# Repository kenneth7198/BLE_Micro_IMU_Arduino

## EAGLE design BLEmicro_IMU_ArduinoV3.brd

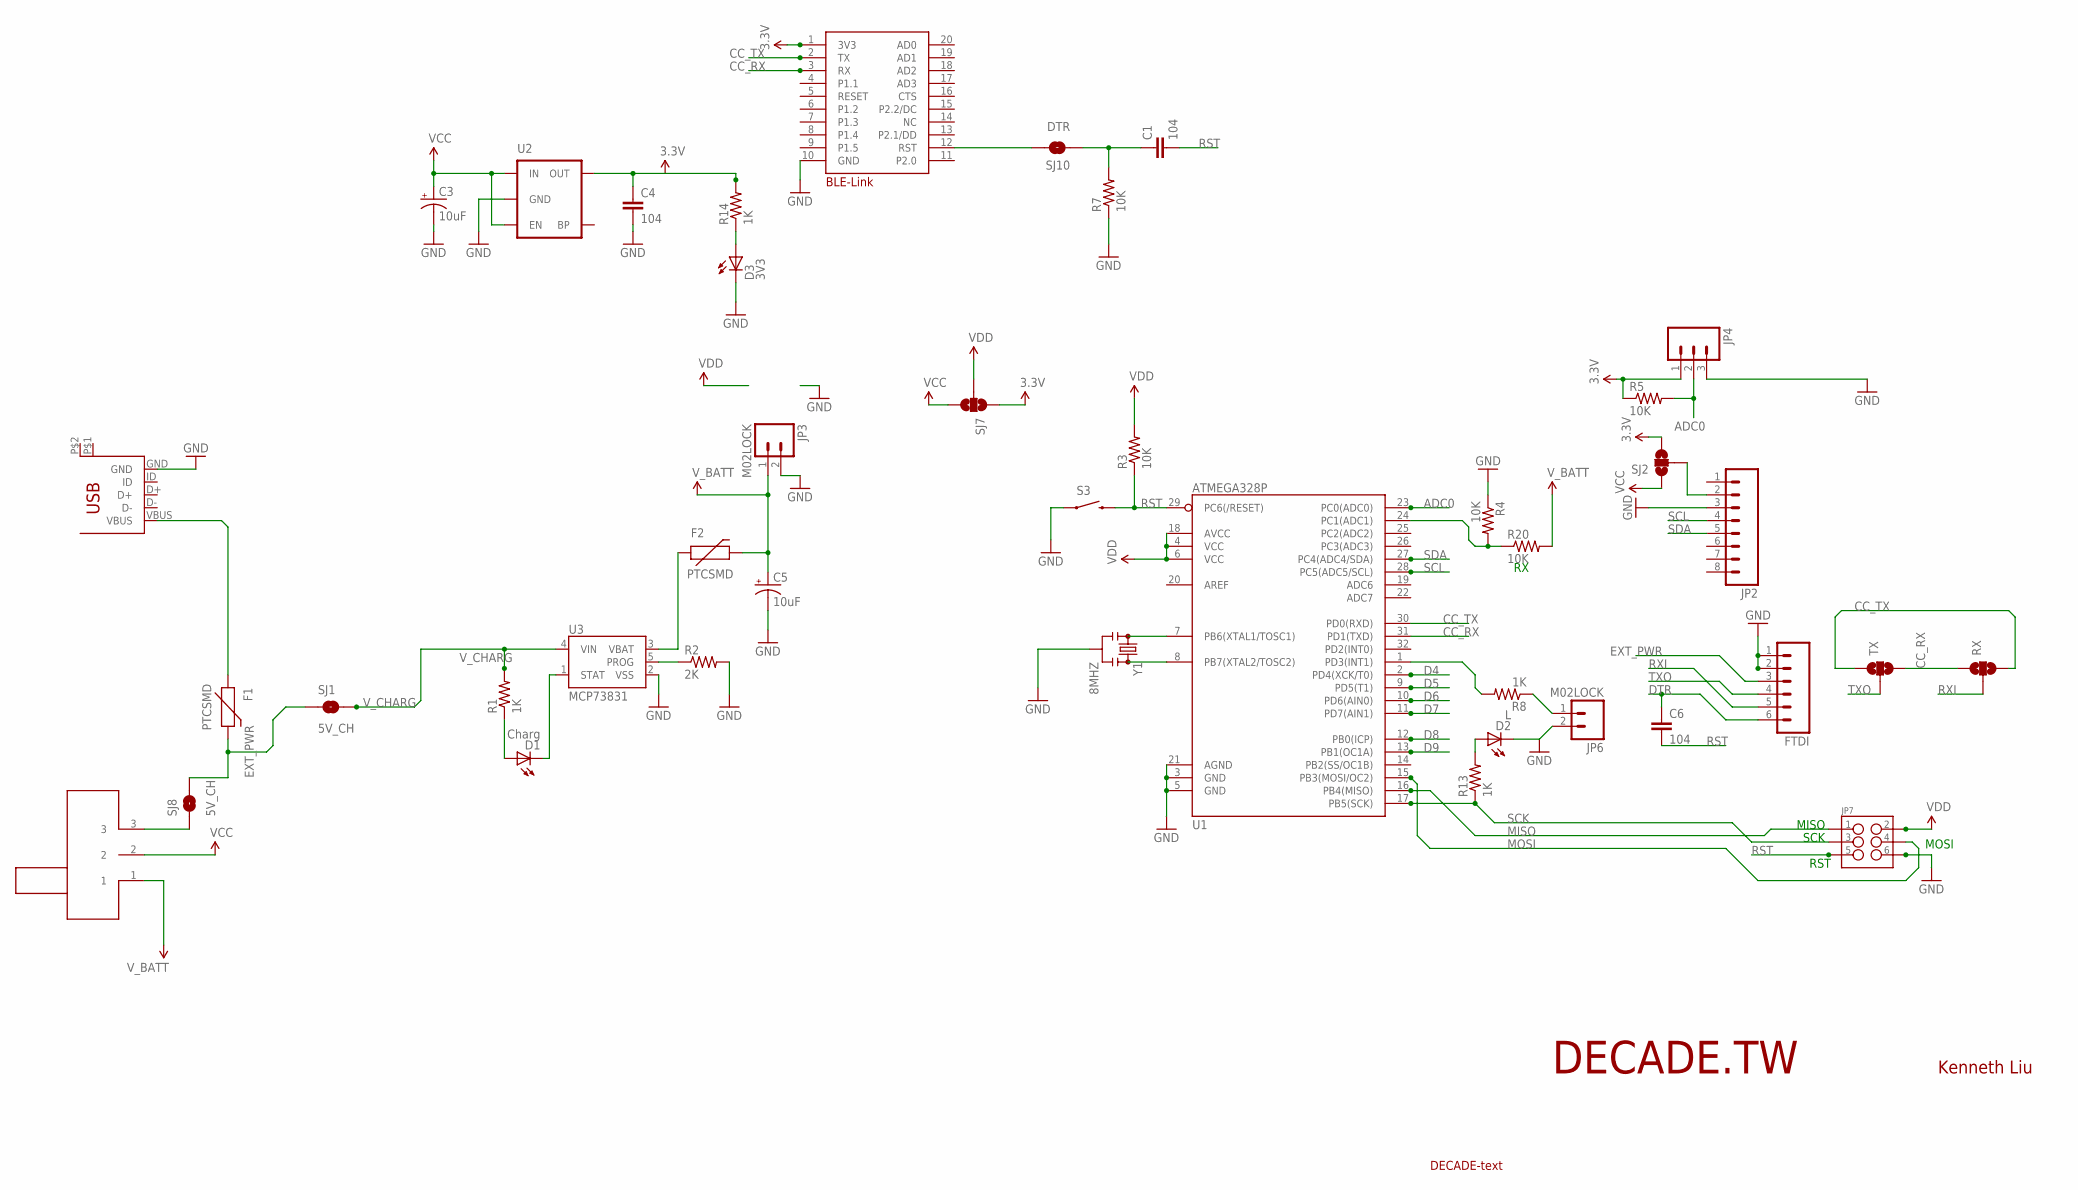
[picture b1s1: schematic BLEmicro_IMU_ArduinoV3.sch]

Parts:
C1, C4, C6: 104; 0603-CAP
C3, C5: 10uF; EIA3216
D1: Charg; LED-0603
D2: L; LED-0603
D3: 3V3; LED-0603
F1, F2: PTCSMD; PTC-1206
FTDI: M06NO_SILK; 1X06_NO_SILK
JP2: M08NO_SILK; 1X08_NO_SILK
JP3, JP6: M02LOCK; 1X02_LOCK
JP4: M03PTH; 1X03
JP7: M03X2NO_SILK; 2X3-NS
R1, R8, R13, R14: 1K; 0603-RES
R2: 2K; 0603-RES
R3, R4, R5, R7, R20: 10K; 0603-RES
RX: SOLDERJUMPER_2WAYS; SJ_3
S3: SWITCH-MOMENTARY-2SMD-1101NE; TACTILE-SWITCH-1101NE
SJ1, SJ8: 5V_CH; SJ_2S
SJ2, SJ7: SOLDERJUMPER_2WAYS; SJ_3
SJ10: DTR; SJ_2S
TX: SOLDERJUMPER_2WAYS; SJ_3
U1: ATMEGA328P; TQFP32-08
U2: MIC52053.3V; SOT23-5
U3: MCP73831; SOT23-5
U$1: BLE-LINK; XBEE-1_LOCK
U$2: USB_MICRO_7PIN; USB-MICROB-7PIN
U$4: DECADE-SW-SMALL; DECADE-SW-SM
U$7: DECADE-LOGO-TEXT
Y1: 8MHZ; RESONATOR-SMD

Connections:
3.3V: C4.1, JP4.1, R5.1, R14.2, SJ2.3, SJ7.1, U2.5 (OUT), U$1.1 (3V3)
ADC0: JP4.2, R5.2, U1.23 (PC0(ADC0))
CC_RX: RX.1, TX.3, U1.31 (PD1(TXD)), U$1.3 (RX)
CC_TX: RX.3, TX.1, U1.30 (PD0(RXD)), U$1.2 (TX)
D4: U1.2 (PD4(XCK/T0))
D5: U1.9 (PD5(T1))
D6: U1.10 (PD6(AIN0))
D7: U1.11 (PD7(AIN1))
D8: U1.12 (PB0(ICP))
D9: U1.13 (PB1(OC1A))
DTR: C6.1, FTDI.6
EXT_PWR: F1.2, FTDI.3, SJ1.1, SJ8.2
GND: C3.C (-), C4.2, C5.C (-), D2.C, D3.C, FTDI.1, FTDI.2, JP2.3, JP3.2, JP4.3, JP6.2, JP7.6, R2.2, R4.1, R7.1, S3.1, U1.3 (GND), U1.5 (GND), U1.21 (AGND), U2.2 (GND), U3.2 (VSS), U$1.10 (GND), U$2.GND, Y1.2
MISO: JP7.1, U1.16 (PB4(MISO))
MOSI: JP7.4, U1.15 (PB3(MOSI/OC2))
unnamed: U1.7 (PB6(XTAL1/TOSC1)), Y1.1
unnamed: U1.8 (PB7(XTAL2/TOSC2)), Y1.3
unnamed: D1.C, U3.1 (STAT)
unnamed: D1.A, R1.1
unnamed: F1.1, U$2.VBUS
unnamed: R2.1, U3.5 (PROG)
unnamed: F2.1, U3.3 (VBAT)
unnamed: D2.A, R13.2
unnamed: D3.A, R14.1
unnamed: C1.1, R7.2, SJ10.1
unnamed: SJ8.1, U$4.3
unnamed: JP2.2, SJ2.2
unnamed: R8.2, U1.1 (PD3(INT1))
unnamed: JP6.1, R8.1
unnamed: R4.2, R20.1, U1.24 (PC1(ADC1))
unnamed: SJ10.2, U$1.12 (RST)
RST: C1.2, C6.2, JP7.5, R3.1, S3.2, U1.29 (PC6(/RESET))
RXI: FTDI.5, RX.2
SCK: JP7.3, R13.1, U1.17 (PB5(SCK))
SCL: JP2.4, U1.28 (PC5(ADC5/SCL))
SDA: JP2.5, U1.27 (PC4(ADC4/SDA))
TXO: FTDI.4, TX.2
VCC: C3.A (+), SJ2.1, SJ7.3, U2.1 (IN), U2.3 (EN), U$4.2
VDD: JP7.2, R3.2, SJ7.2, U1.4 (VCC), U1.6 (VCC), U1.18 (AVCC)
V_BATT: C5.A (+), F2.2, JP3.1, R20.2, U$4.1
V_CHARG: R1.2, SJ1.2, U3.4 (VIN)

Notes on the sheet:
RST
MOSI
SCK
MISO
DECADE.TW
Kenneth Liu

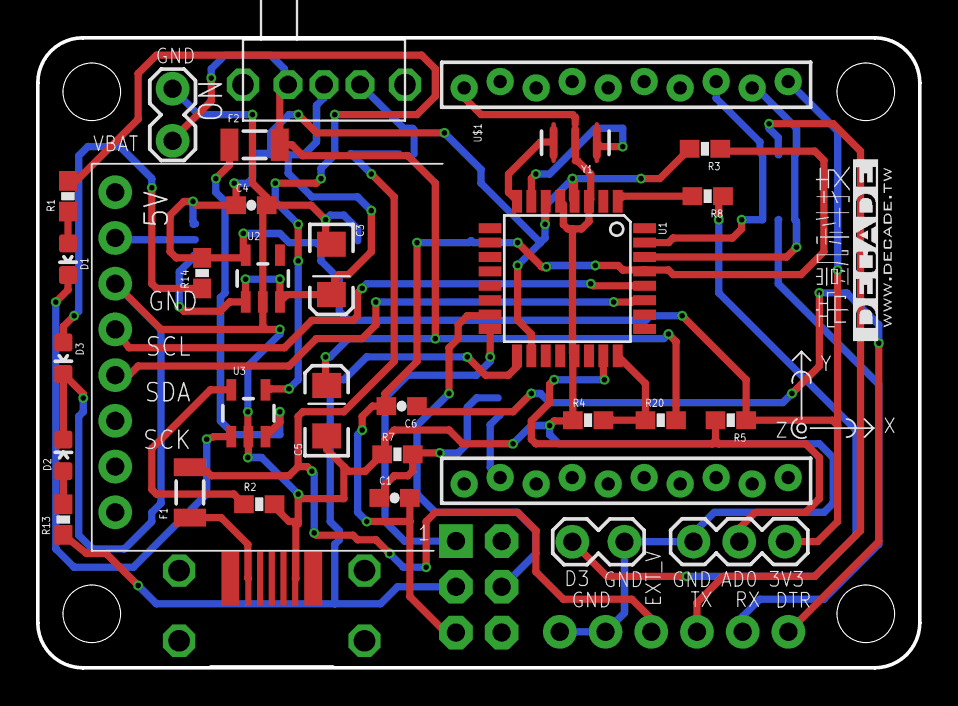
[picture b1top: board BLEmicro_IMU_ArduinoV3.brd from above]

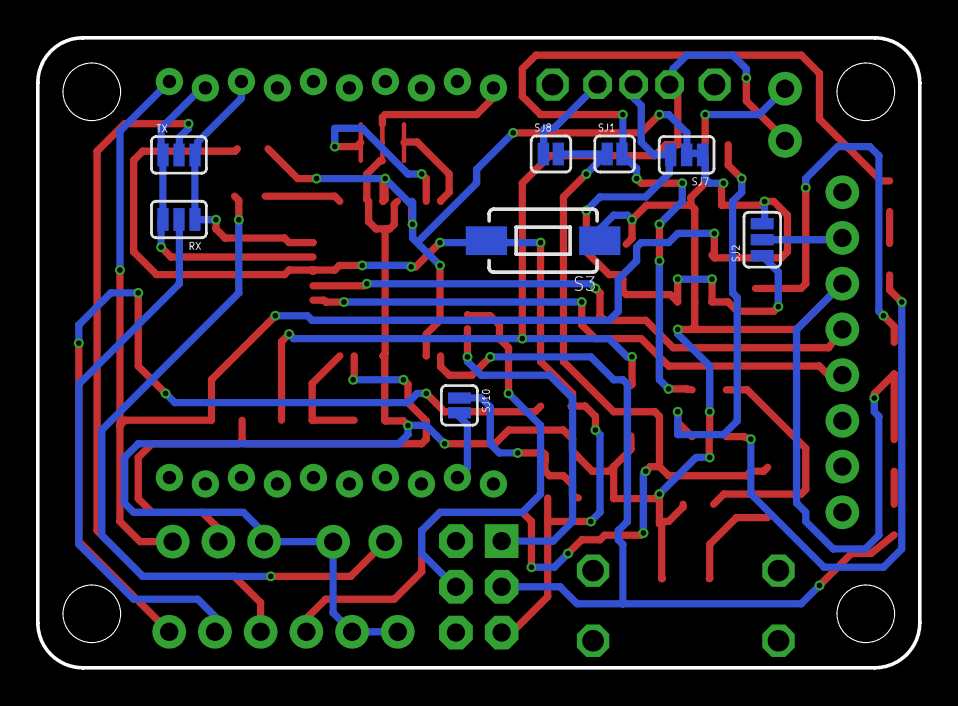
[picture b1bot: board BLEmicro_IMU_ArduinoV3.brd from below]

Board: 2 copper layers, 49.0 x 35.0 mm, 42 parts (8 on the bottom side), 35 nets.

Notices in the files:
parts and their libraries:
SparkFun-DigitalIC: Licensing: Creative Commons ShareAlike 4.0 International - https://creativecommons.org/licenses/by-sa/4.0
DECADE-libraries: Licensing: CC v3.0 Share-Alike You are welcome to use this library for commercial purposes.
